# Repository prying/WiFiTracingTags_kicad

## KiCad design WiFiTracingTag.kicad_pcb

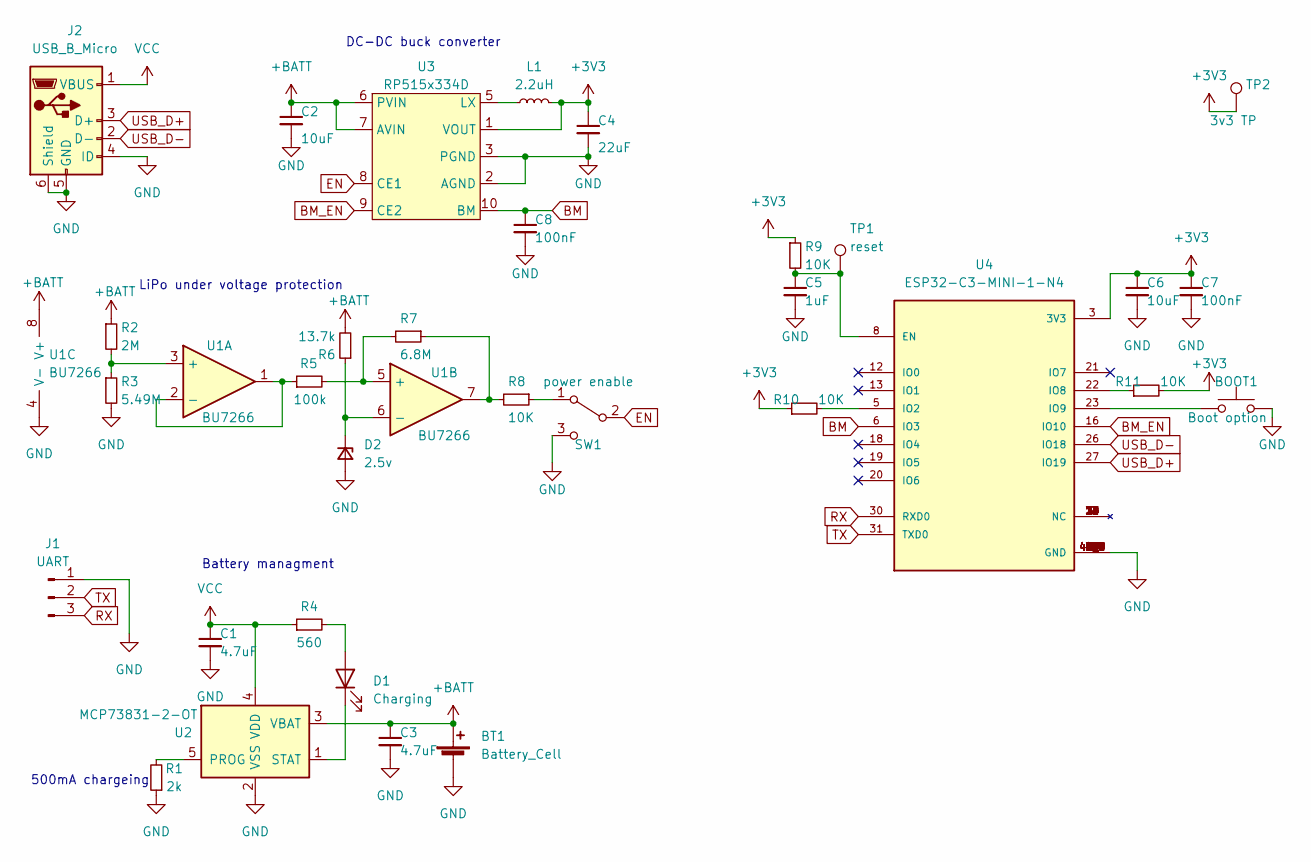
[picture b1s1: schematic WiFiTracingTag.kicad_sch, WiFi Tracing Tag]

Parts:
BOOT1: Boot option; SW_SPST_ck_PTS636; MPN RKB2SJM250SMTR LFS
BT1: Battery_Cell; JST_PH_S2B-PH-SM4-TB_1x02-1MP_P2.00mm_Horizontal; MPN JST-PH 2-Pin
C1, C3: 4.7uF; C_0603_1608Metric; MPN CL10A475KP8NNNC
C2, C6: 10uF; C_0603_1608Metric; MPN JMK107ABJ106KA-T
C4: 22uF; C_0603_1608Metric; MPN JMK107BBJ226MA-T
C5: 1uF; C_0603_1608Metric; MPN CL10B105KP8NNNC
C7, C8: 100nF; C_0603_1608Metric; MPN 06036C104KAT4A
D1: Charging; D_0603_1608Metric; MPN B1911USD-20D000114U1930
D2: 2.5v; SOT-23; MPN LM4040DYM3-2.5
J1: UART; PinHeader_1x03_P2.54mm_Vertical; MPN PREC003SBAN-M71RC
J2: USB_B_Micro; USB_Micro_AdamTech_MCR-B-S-RA-SMT-CS14; MPN MCR-B-S-RA-SMT-CS14-T/R
L1: 2.2uH; L_Murata_DEF20160P-xxxM=P2_2.0x1.6mm; MPN DFE201610P-2R2M=P2
R1: 2k; R_0603_1608Metric; MPN RC1608F202CS
R2: 2M; R_0603_1608Metric; MPN RK73H1JTTD2004F
R3: 5.49M; R_0603_1608Metric; MPN CRCW06035M49FKEA
R4: 560; R_0603_1608Metric; MPN ERJ-3GEYJ561V
R5: 100k; R_0603_1608Metric; MPN AF0603FR-07100KL
R6: 13.7k; R_0603_1608Metric; MPN ERJ-3EKF1372V
R7: 6.8M; R_0603_1608Metric; MPN AC0603FR-076M8L
R8, R9, R10, R11: 10K; R_0603_1608Metric; MPN RC1608F103CS
SW1: power enable; SW_SPDT_CK-JS202011JAQN; MPN JS202011JAQN
TP1: reset; TestPoint_Pad_D1.5mm
TP2: 3v3 TP; TestPoint_Pad_D1.5mm
U1: BU7266; MSOP-8_3x3mm_P0.65mm; MPN BU7266FVM
U2: MCP73831-2-OT; SOT-23-5; MPN MCP73831T-2ACI/OT
U3: RP515x334D; Nisshinbo_DFN(PLP)-10_2.7x2.5mm_P0.5mm; MPN RP515K334D
U4: ESP32-C3-MINI-1-N4; XCVR_ESP32-C3-MINI-1-N4; PARTREV v1.0

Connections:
+3V3: C4.1, C6.1, C7.1, L1.2, R9.1, R10.1, R11.2, TP2.1, U3.1 (VOUT), U4.3 (3V3)
+BATT: BT1.2 (+), C2.1, C3.1, R2.1, R6.2, U1.8 (V+), U2.3 (VBAT), U3.6 (PVIN), U3.7 (AVIN)
BM: C8.1, U3.10 (BM), U4.6 (IO3)
BM_EN: U3.9 (CE2), U4.16 (IO10)
EN: SW1.2 (B), U3.8 (CE1)
GND: BOOT1.2, BT1.1 (-), C1.2, C2.2, C3.2, C4.2, C5.2, C6.2, C7.2, C8.2, D2.2 (A), J1.1, J2.4 (ID), J2.5 (GND), J2.6 (Shield), R1.1, R3.2, SW1.3 (C), U1.4 (V-), U2.2 (VSS), U3.2 (AGND), U3.3 (PGND), U3.11 (PGND), U4.1 (GND), U4.2 (GND), U4.11 (GND), U4.14 (GND), U4.36 (GND), U4.37 (GND), U4.38 (GND), U4.39 (GND), U4.40 (GND), U4.41 (GND), U4.42 (GND), U4.43 (GND), U4.44 (GND), U4.45 (GND), U4.46 (GND), U4.47 (GND), U4.48 (GND), U4.49_1 (GND), U4.49_2 (GND), U4.49_3 (GND), U4.49_4 (GND), U4.49_5 (GND), U4.49_6 (GND), U4.49_7 (GND), U4.49_8 (GND), U4.49_9 (GND), U4.50 (GND), U4.51 (GND), U4.52 (GND), U4.53 (GND)
unnamed: BOOT1.1, U4.23 (IO9)
unnamed: C5.1, R9.2, TP1.1, U4.8 (EN)
unnamed: D1.1 (K), U2.1 (STAT)
unnamed: D1.2 (A), R4.2
unnamed: D2.1 (K), R6.1, U1.6 (-)
unnamed: L1.1, U3.4 (LX), U3.5 (LX)
unnamed: R1.2, U2.5 (PROG)
unnamed: R2.2, R3.1, U1.3 (+)
unnamed: R5.1, U1.1, U1.2 (-)
unnamed: R5.2, R7.2, U1.5 (+)
unnamed: R7.1, R8.2, U1.7
unnamed: R8.1, SW1.1 (A)
unnamed: R10.2, U4.5 (IO2)
unnamed: R11.1, U4.22 (IO8)
RX: J1.3, U4.30 (RXD0)
TX: J1.2, U4.31 (TXD0)
USB_D+: J2.3 (D+), U4.27 (IO19)
USB_D-: J2.2 (D-), U4.26 (IO18)
VCC: C1.1, J2.1 (VBUS), R4.1, U2.4 (VDD)

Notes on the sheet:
Battery managment
LiPo under voltage protection
DC-DC buck converter
500mA chargeing

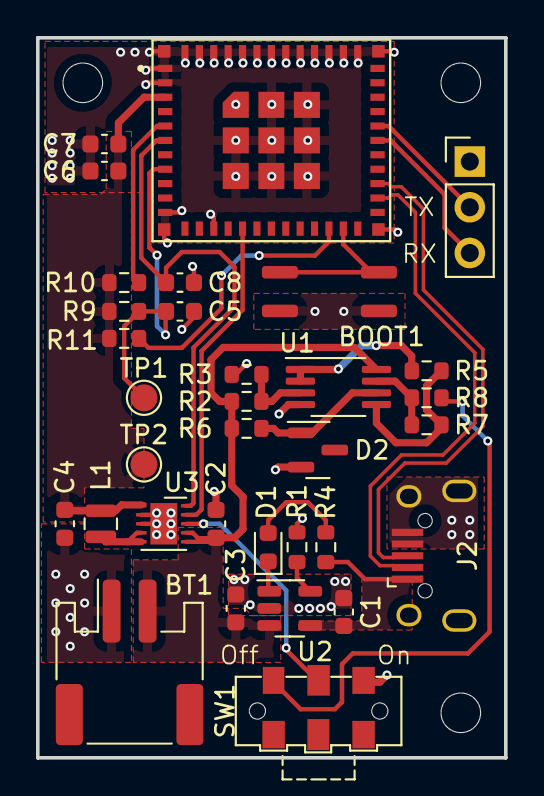
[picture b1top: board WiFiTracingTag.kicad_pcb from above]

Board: 2 copper layers, 26.0 x 40.0 mm, 33 parts (0 on the bottom side), 25 nets.
